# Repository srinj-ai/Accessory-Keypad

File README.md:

# Accessory Keypad (Hakpad)

A custom macro keypad designed for all your productivity and creative needs—whether it's coding, 3D modeling, PCB design, or gaming. Fully customizable to fit your exact workflow.

---

---

## Features

- **4 Programmable Keys:** Dedicated mechanical switches for custom shortcuts, macros, or quick actions.
- **Rotary Encoder:** Precision control knob ideal for fine value adjustments, scrolling, brush resizing, or volume control.
- **0.96" OLED Display:** Displays current mode, active key bindings, or custom status.
- **Multi-Mode Support:** Switch seamlessly between tailored modes for coding, 3D modeling, PCB design, and gaming.
- **Fully Customizable:** Rebind keys and rotary controls to match your personal setup and workflow.

---

## Bill of Materials (BOM)

| Component | Quantity |
| :--- | :---: |
| Seeed Studio XIAO RP2040 | 1 |
| MX-compatible mechanical switches | 4 |
| MX keycaps | 4 |
| EC11 rotary encoder | 1 |
| Encoder knob | 1 |
| 0.96" SSD1306 OLED display (128×64, I2C) | 1 |
| USB-C cable | 1 |

*For complete details, see [`materials.txt`](materials.txt).*

---

## Repository Structure

```
.
├── assets/
│   └── pcb.webp
├── case/
│   ├── plate.3mf
│   └── tray.3mf
├── pcb/
│   ├── hakpad.kicad_pcb
│   ├── hakpad.kicad_sch
│   └── hakpad-F_Silkscreen.zip
├── LICENSE
├── README.md
└── materials.txt
```

---

## Customization

Since the project is powered by the Seeed Studio XIAO RP2040, you can program it using standard RP2040 firmware frameworks (such as QMK, KMK, CircuitPython, or Arduino). Custom keymaps and display routines can be configured to match your specific application requirements.

---

## Use of AI

- Bug fixes and troubleshooting.
- Guidance throughout project planning and implementation.

---

## License

This project is licensed under the [MIT License](LICENSE).

---

## Credits

- Designed and programmed by [Srinjoy Das](https://github.com/srinj-ai)

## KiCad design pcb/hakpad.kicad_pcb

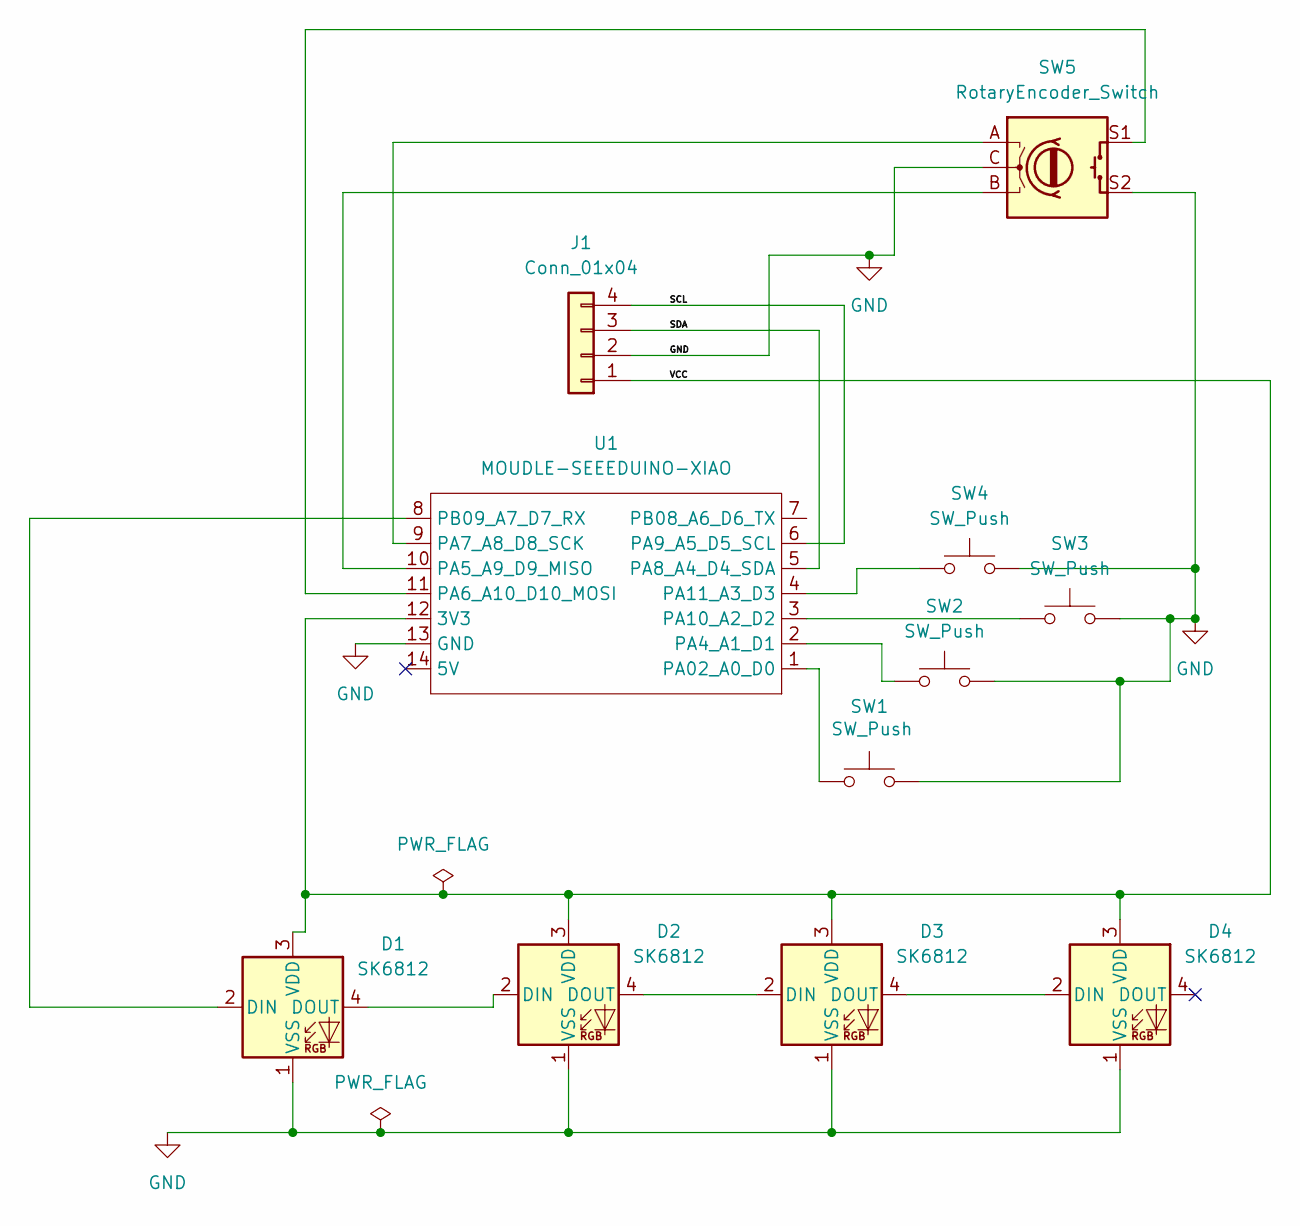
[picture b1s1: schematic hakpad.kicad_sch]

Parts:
D1, D2, D3, D4: SK6812; LED_SK6812_PLCC4_5.0x5.0mm_P3.2mm
J1: Conn_01x04; PinHeader_1x04_P2.54mm_Vertical
SW1, SW2, SW3, SW4: SW_Push; SW_Cherry_MX_1.00u_PCB
SW5: RotaryEncoder_Switch; RotaryEncoder_Alps_EC11E_Vertical_H20mm
U1: MOUDLE-SEEEDUINO-XIAO; XIAO-Generic-Hybrid-14P-2.54-21X17.8MM

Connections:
/SCL: J1.4, U1.6 (PA9_A5_D5_SCL)
/SDA: J1.3, U1.5 (PA8_A4_D4_SDA)
/VCC: D1.3 (VDD), D2.3 (VDD), D3.3 (VDD), D4.3 (VDD), J1.1, U1.12 (3V3)
GND: D1.1 (VSS), D2.1 (VSS), D3.1 (VSS), D4.1 (VSS), J1.2, SW1.2, SW2.2, SW3.2, SW4.2, SW5.C, SW5.S2, U1.13 (GND)
unnamed: D1.2 (DIN), U1.8 (PB09_A7_D7_RX)
unnamed: D1.4 (DOUT), D2.2 (DIN)
unnamed: D2.4 (DOUT), D3.2 (DIN)
unnamed: D3.4 (DOUT), D4.2 (DIN)
unnamed: SW1.1, U1.1 (PA02_A0_D0)
unnamed: SW2.1, U1.2 (PA4_A1_D1)
unnamed: SW5.B, U1.10 (PA5_A9_D9_MISO)
unnamed: SW5.S1, U1.11 (PA6_A10_D10_MOSI)
unnamed: SW5.A, U1.9 (PA7_A8_D8_SCK)
unnamed: SW3.1, U1.3 (PA10_A2_D2)
unnamed: SW4.1, U1.4 (PA11_A3_D3)

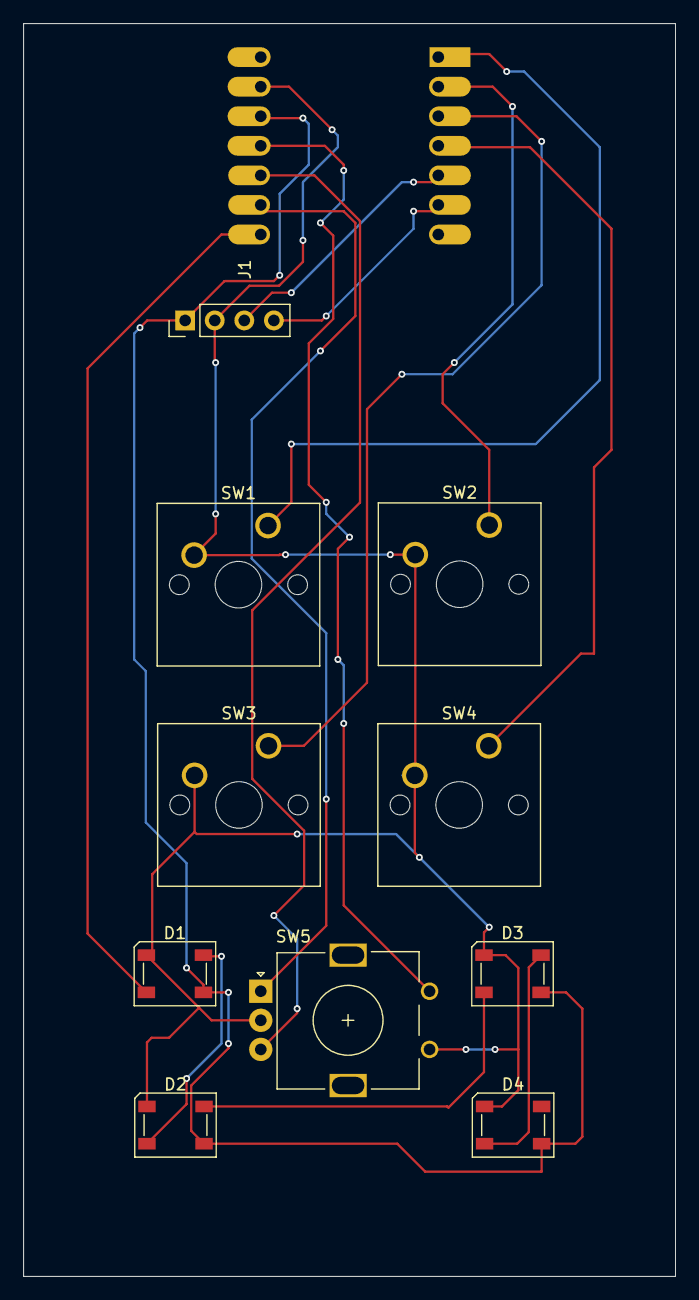
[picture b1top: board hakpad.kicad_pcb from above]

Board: 2 copper layers, 56.0 x 107.6 mm, 11 parts (1 on the bottom side), 15 nets.

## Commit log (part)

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2026-06-24 added pcb holes
2026-06-24 added a better readme
2026-06-25 add new gr
2026-06-26 Rename ac1d0551-b509-4d9d-8b45-528ae08200c3.webp to pcb.webp
2026-06-26 Add materials list for project components
